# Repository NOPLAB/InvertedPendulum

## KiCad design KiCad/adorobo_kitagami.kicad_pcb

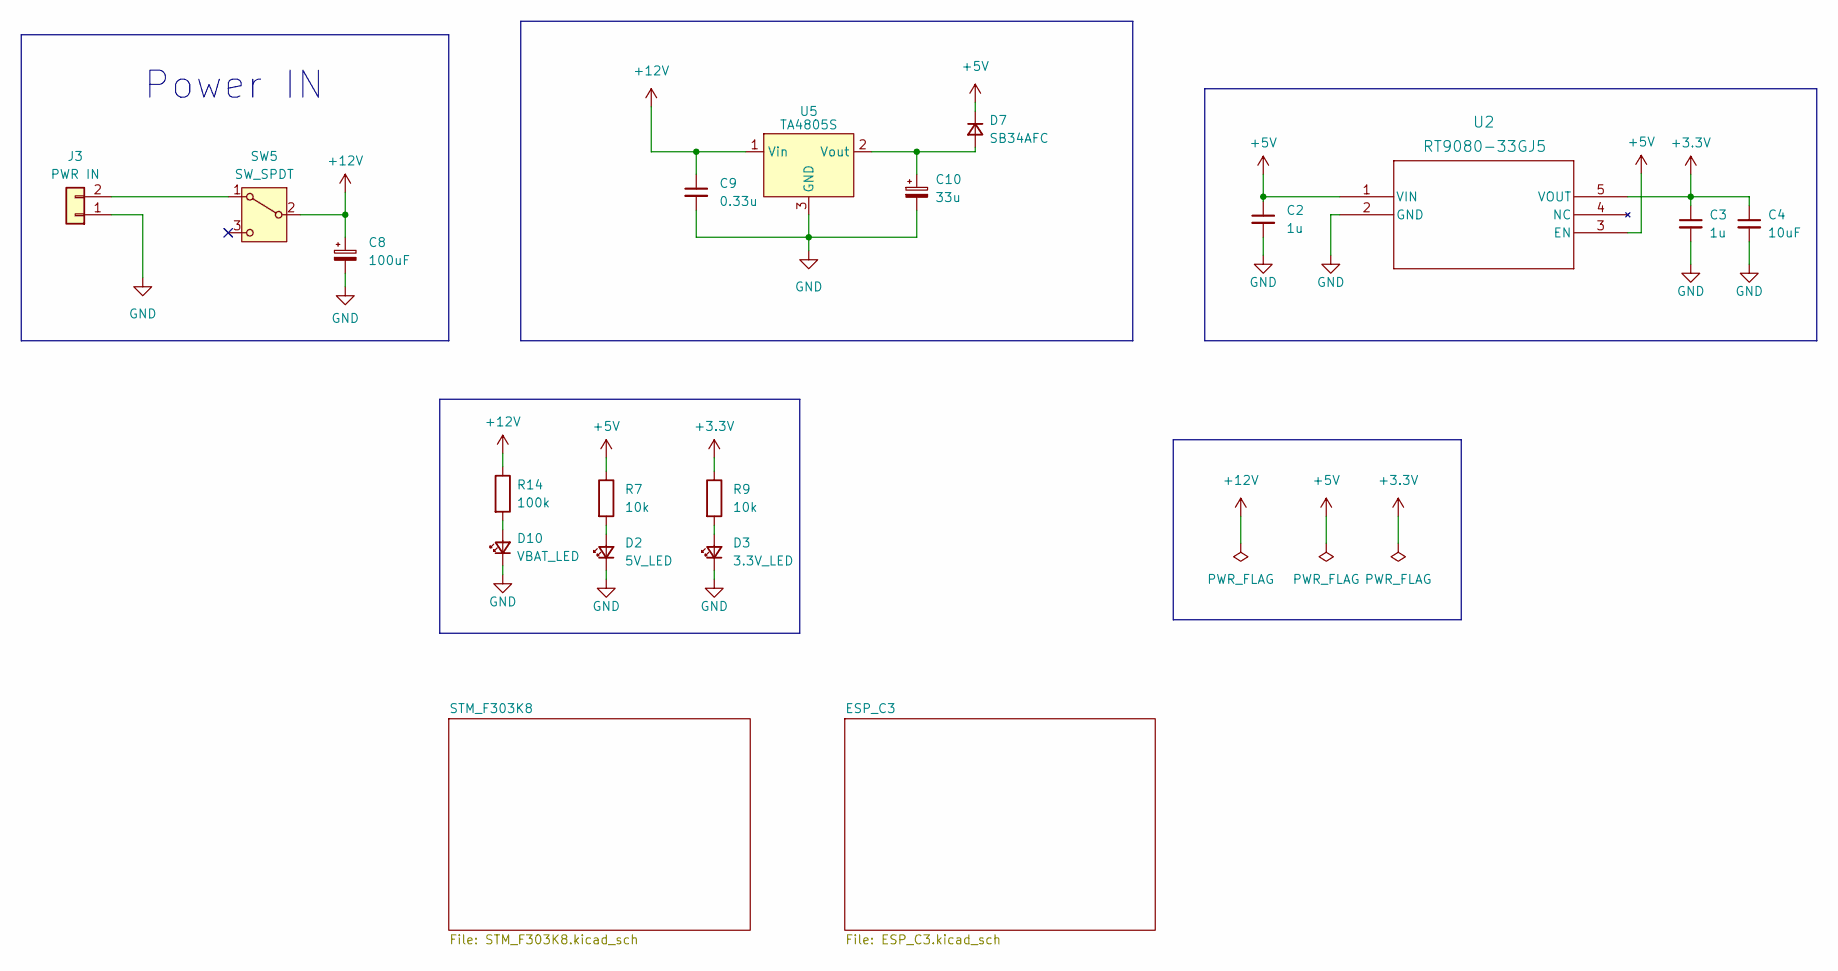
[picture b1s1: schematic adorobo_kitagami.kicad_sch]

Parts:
C2, C3: 1u; C_0603_1608Metric_Pad1.08x0.95mm_HandSolder
C4: 10uF; C_0805_2012Metric_Pad1.18x1.45mm_HandSolder
C8: 100uF; CP_Radial_D5.0mm_P2.00mm
C9: 0.33u; C_Radial_D10.0mm_H12.5mm_P5.00mm
C10: 33u; CP_Radial_D5.0mm_P2.00mm
D2: 5V_LED; LED_0603_1608Metric_Pad1.05x0.95mm_HandSolder
D3: 3.3V_LED; LED_0603_1608Metric_Pad1.05x0.95mm_HandSolder
D7: SB34AFC; SODFL4725X110N
D10: VBAT_LED; LED_0603_1608Metric_Pad1.05x0.95mm_HandSolder
J3: PWR IN; JST_XA_B02B-XASK-1_1x02_P2.50mm_Vertical
R7, R9: 10k; R_0603_1608Metric_Pad0.98x0.95mm_HandSolder
R14: 100k; R_0603_1608Metric_Pad0.98x0.95mm_HandSolder
SW5: SW_SPDT; 2MS1T1B4VS2QES
U2: RT9080-33GJ5
U5: TA4805S

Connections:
+3.3V: C3.1, C4.1, R9.1, U2.5 (VOUT); also elsewhere on the board
+5V: C2.1, D7.1 (K), R7.1, U2.1 (VIN), U2.3 (EN); also elsewhere on the board
+12V: C8.1, C9.1, R14.1, SW5.2 (B), U5.1 (Vin); also elsewhere on the board
GND: C2.2, C3.2, C4.2, C8.2, C9.2, C10.2, D2.1 (K), D3.1 (K), D10.1 (K), J3.1, U2.2 (GND), U5.3 (GND); also elsewhere on the board
unnamed: D2.2 (A), R7.2
unnamed: D3.2 (A), R9.2
unnamed: C10.1, D7.2 (A), U5.2 (Vout)
unnamed: D10.2 (A), R14.2
unnamed: J3.2, SW5.1 (A)

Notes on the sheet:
Power IN

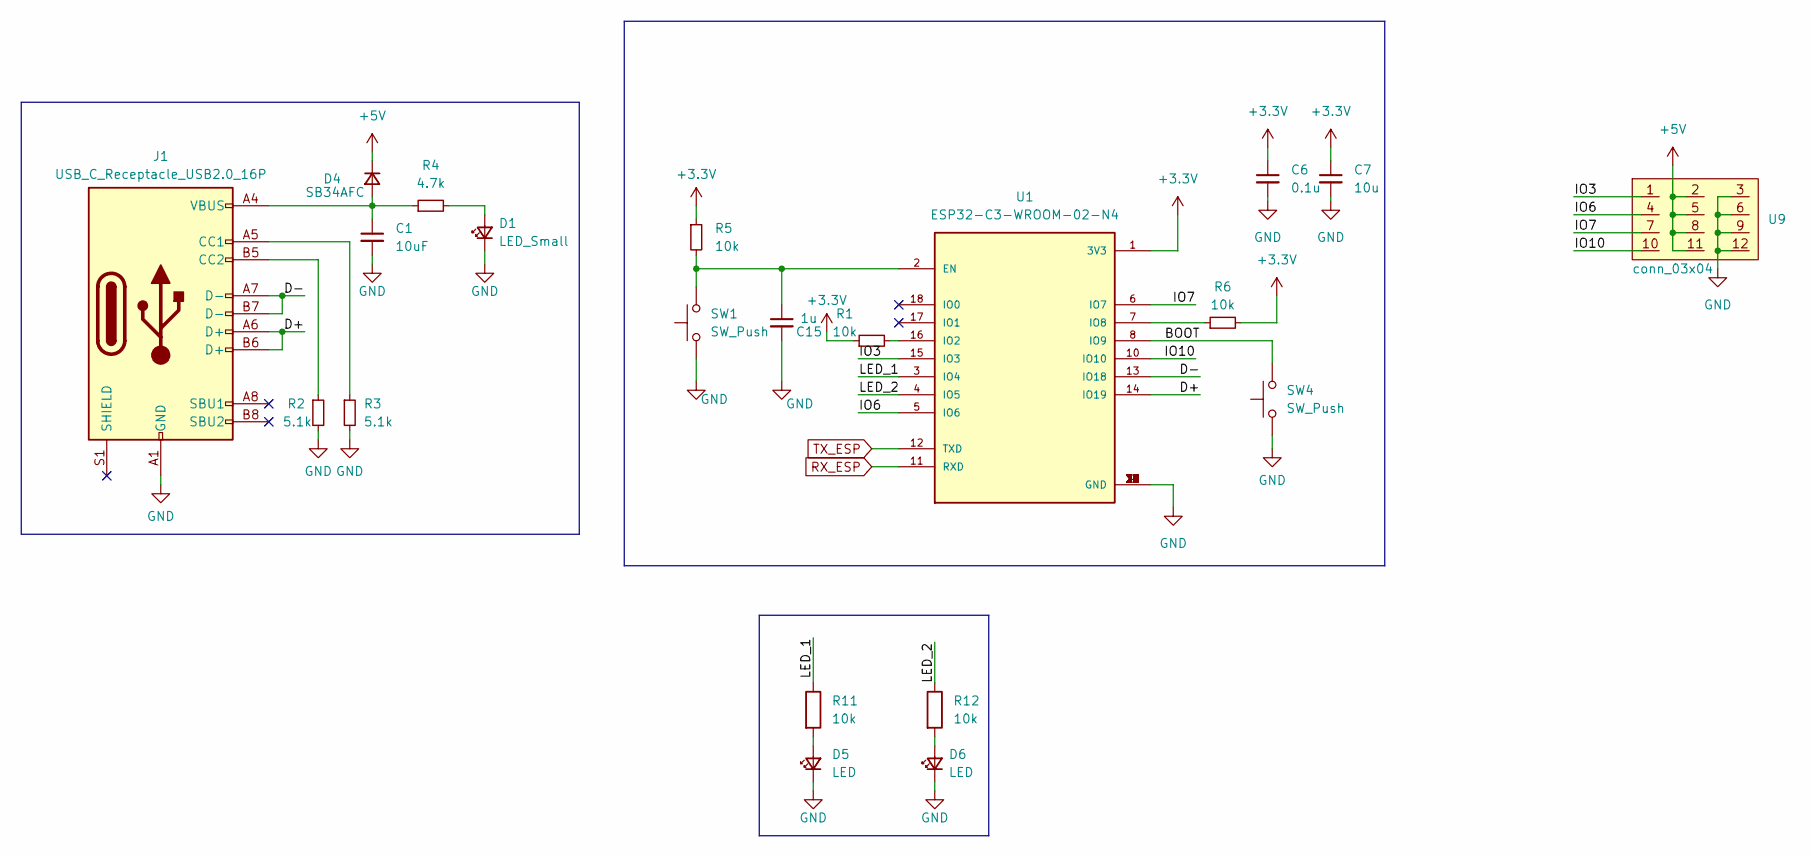
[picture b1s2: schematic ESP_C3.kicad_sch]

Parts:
C1: 10uF; R_0805_2012Metric_Pad1.20x1.40mm_HandSolder
C6: 0.1u; C_0603_1608Metric_Pad1.08x0.95mm_HandSolder
C7: 10u; R_0805_2012Metric_Pad1.20x1.40mm_HandSolder
C15: 1u; C_0603_1608Metric_Pad1.08x0.95mm_HandSolder
D1: LED_Small; LED_0603_1608Metric_Pad1.05x0.95mm_HandSolder
D4: SB34AFC; SODFL4725X110N
D5, D6: LED; LED_0603_1608Metric_Pad1.05x0.95mm_HandSolder
J1: USB_C_Receptacle_USB2.0_16P; HCTYPEC16PCB10
R1, R5, R6, R11, R12: 10k; R_0603_1608Metric_Pad0.98x0.95mm_HandSolder
R2, R3: 5.1k; R_0603_1608Metric_Pad0.98x0.95mm_HandSolder
R4: 4.7k; R_0603_1608Metric_Pad0.98x0.95mm_HandSolder
SW1, SW4: SW_Push; SKRPACE010
U1: ESP32-C3-WROOM-02-N4; MODULE_ESP32-C3-WROOM-02-H4
U9: conn_03x04; conn_03x04_pinn

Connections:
+3.3V: C6.1, C7.1, R1.1, R5.1, R6.2, U1.1 (3V3); also elsewhere on the board
+5V: D4.1 (K), U9.2, U9.5, U9.8, U9.11; also elsewhere on the board
/ESP_C3/BOOT: SW4.2, U1.8 (IO9)
/ESP_C3/D+: J1.A6 (D+), J1.B6 (D+), U1.14 (IO19)
/ESP_C3/D-: J1.A7 (D-), J1.B7 (D-), U1.13 (IO18)
/ESP_C3/IO3: U1.15 (IO3), U9.1
/ESP_C3/IO6: U1.5 (IO6), U9.4
/ESP_C3/IO7: U1.6 (IO7), U9.7
/ESP_C3/IO10: U1.10 (IO10), U9.10
/ESP_C3/LED_1: R11.1, U1.3 (IO4)
/ESP_C3/LED_2: R12.1, U1.4 (IO5)
GND: C1.2, C6.2, C7.2, C15.2, D1.1 (K), D5.1 (K), D6.1 (K), J1.A1 (GND), J1.A12 (GND), J1.B1 (GND), J1.B12 (GND), R2.2, R3.2, SW1.1, SW4.1, U1.9 (GND), U1.19 (GND), U1.20 (GND), U1.21 (GND), U1.22 (GND), U1.23 (GND), U1.24 (GND), U1.25 (GND), U1.26 (GND), U1.27 (GND), U1.28 (GND), U1.29 (GND), U1.30 (GND), U1.31 (GND), U1.32 (GND), U1.33 (GND), U1.34 (GND), U1.35 (GND), U1.36 (GND), U1.37 (GND), U1.38 (GND), U1.39 (GND), U9.3, U9.6, U9.9, U9.12; also elsewhere on the board
unnamed: D1.2 (A), R4.2
unnamed: C1.1, D4.2 (A), J1.A4 (VBUS), J1.A9 (VBUS), J1.B4 (VBUS), J1.B9 (VBUS), R4.1
unnamed: D5.2 (A), R11.2
unnamed 45: D6.2 (A), R12.2; also elsewhere on the board
unnamed: J1.A5 (CC1), R3.1
unnamed: J1.B5 (CC2), R2.1
unnamed: C15.1, R5.2, SW1.2, U1.2 (EN)
unnamed: R1.2, U1.16 (IO2)
unnamed: R6.1, U1.7 (IO8)
RX_ESP: U1.11 (RXD); also elsewhere on the board
TX_ESP: U1.12 (TXD); also elsewhere on the board

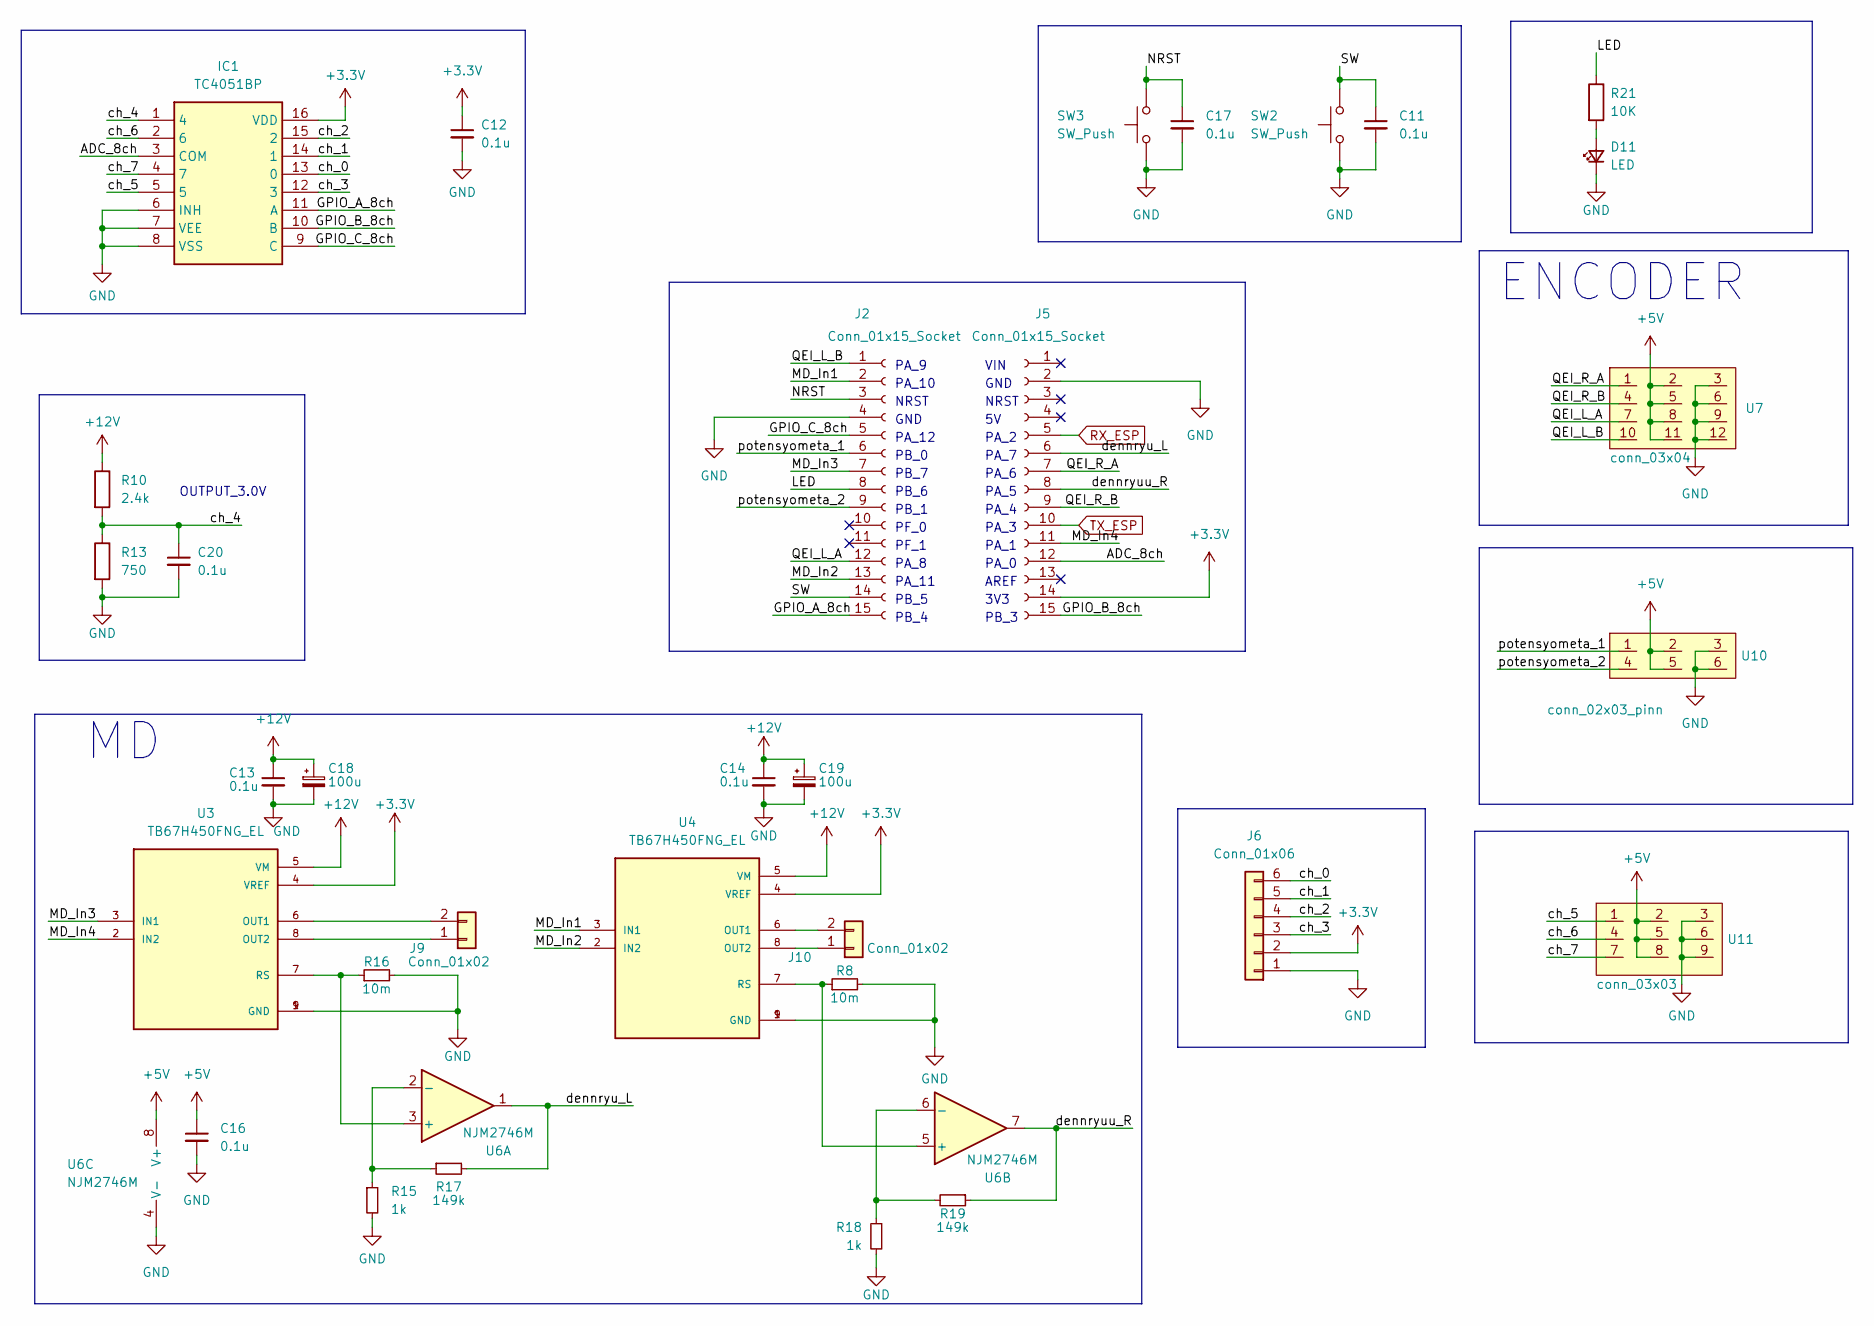
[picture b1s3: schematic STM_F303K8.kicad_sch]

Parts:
C11, C12, C13, C14, C16, C17, C20: 0.1u; C_0603_1608Metric_Pad1.08x0.95mm_HandSolder
C18, C19: 100u; CP_Radial_D5.0mm_P2.00mm
D11: LED; LED_0603_1608Metric_Pad1.05x0.95mm_HandSolder
IC1: TC4051BP; DIP762W60P254L1925H445Q16N; Manufacturer_Part_Number TC4051BP; Mouser Part Number N/A
J2, J5: Conn_01x15_Socket; PinSocket_1x15_P2.54mm_Vertical
J6: Conn_01x06; JST_PH_B6B-PH-K_1x06_P2.00mm_Vertical
J9, J10: Conn_01x02; JST_XA_B02B-XASK-1_1x02_P2.50mm_Vertical
R8, R16: 10m; SL1TER010F
R10: 2.4k; R_0603_1608Metric_Pad0.98x0.95mm_HandSolder
R13: 750; R_0603_1608Metric_Pad0.98x0.95mm_HandSolder
R15, R18: 1k; R_0603_1608Metric_Pad0.98x0.95mm_HandSolder
R17, R19: 149k; R_0603_1608Metric_Pad0.98x0.95mm_HandSolder
R21: 10K; R_0603_1608Metric_Pad0.98x0.95mm_HandSolder
SW2, SW3: SW_Push; DTS63NV
U3, U4: TB67H450FNG_EL; SOIC127P599X175-9N
U6: NJM2746M
U7: conn_03x04; conn_03x04_pinn
U10: conn_02x03_pinn; PinHeader_2x03_P2.54mm_Vertical
U11: conn_03x03

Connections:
+3.3V: C12.1, IC1.16 (VDD), J5.1, J5.14, J6.2, U3.4 (VREF), U4.4 (VREF); also elsewhere on the board
+5V: C16.1, U6.8 (V+), U7.2, U7.5, U7.8, U7.11, U10.2, U10.5, U11.2, U11.5, U11.8; also elsewhere on the board
+12V: C13.1, C14.1, C18.1, C19.1, R10.1, U3.5 (VM), U4.5 (VM); also elsewhere on the board
/STM_F303K8/ADC_8ch: IC1.3 (COM), J5.12
/STM_F303K8/GPIO_A_8ch: IC1.11 (A), J2.15
/STM_F303K8/GPIO_B_8ch: IC1.10 (B), J5.15
/STM_F303K8/GPIO_C_8ch: IC1.9 (C), J2.5
/STM_F303K8/LED: J2.8, R21.1
/STM_F303K8/MD_In1: J2.2, U4.3 (IN1)
/STM_F303K8/MD_In2: J2.13, U4.2 (IN2)
/STM_F303K8/MD_In3: J2.7, U3.3 (IN1)
/STM_F303K8/MD_In4: J5.11, U3.2 (IN2)
/STM_F303K8/NRST: C17.1, J2.3, SW3.2
/STM_F303K8/QEI_L_A: J2.12, U7.7
/STM_F303K8/QEI_L_B: J2.1, U7.10
/STM_F303K8/QEI_R_A: J5.7, U7.1
/STM_F303K8/QEI_R_B: J5.9, U7.4
/STM_F303K8/SW: C11.1, J2.14, SW2.2
/STM_F303K8/ch_0: IC1.13 (0), J6.6
/STM_F303K8/ch_1: IC1.14 (1), J6.5
/STM_F303K8/ch_2: IC1.15 (2), J6.4
/STM_F303K8/ch_3: IC1.12 (3), J6.3
/STM_F303K8/ch_4: C20.1, IC1.1 (4), R10.2, R13.1
/STM_F303K8/ch_5: IC1.5, U11.1
/STM_F303K8/ch_6: IC1.2 (6), U11.4
/STM_F303K8/ch_7: IC1.4 (7), U11.7
/STM_F303K8/dennryu_L: J5.6, R17.2, U6.1
/STM_F303K8/dennryuu_R: J5.8, R19.1, U6.7
/STM_F303K8/potensyometa_1: J2.6, U10.1
/STM_F303K8/potensyometa_2: J2.9, U10.4
GND: C11.2, C12.2, C13.2, C14.2, C16.2, C17.2, C18.2, C19.2, C20.2, D11.1 (K), IC1.6 (INH), IC1.7 (VEE), IC1.8 (VSS), J2.4, J5.2, J6.1, R8.2, R13.2, R15.2, R16.2, R18.2, SW2.1, SW3.1, U3.1 (GND), U3.9 (GND), U4.1 (GND), U4.9 (GND), U6.4 (V-), U7.3, U7.6, U7.9, U7.12, U10.3, U10.6, U11.3, U11.6, U11.9; also elsewhere on the board
unnamed: D11.2 (A), R21.2
unnamed: J9.1, U3.8 (OUT2)
unnamed: J9.2, U3.6 (OUT1)
unnamed: J10.1, U4.8 (OUT2)
unnamed: J10.2, U4.6 (OUT1)
unnamed: R16.1, U3.7 (RS), U6.3 (+)
unnamed: R8.1, U4.7 (RS), U6.5 (+)
unnamed: R15.1, R17.1, U6.2 (-)
unnamed: R18.1, R19.2, U6.6 (-)
RX_ESP: J5.5; also elsewhere on the board
TX_ESP: J5.10; also elsewhere on the board

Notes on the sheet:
GND
PB_0
PF_0
PA_7
PA_9
PA_0
PB_6
AREF
VIN
PA_2
PA_1
PA_4
PA_10
PA_8
OUTPUT_3.0V
PB_3
PA_12
PB_7
PB_4
PF_1
NRST
PA_11
PB_5
PA_5
3V3
PA_3
ENCODER
PB_1
PA_6

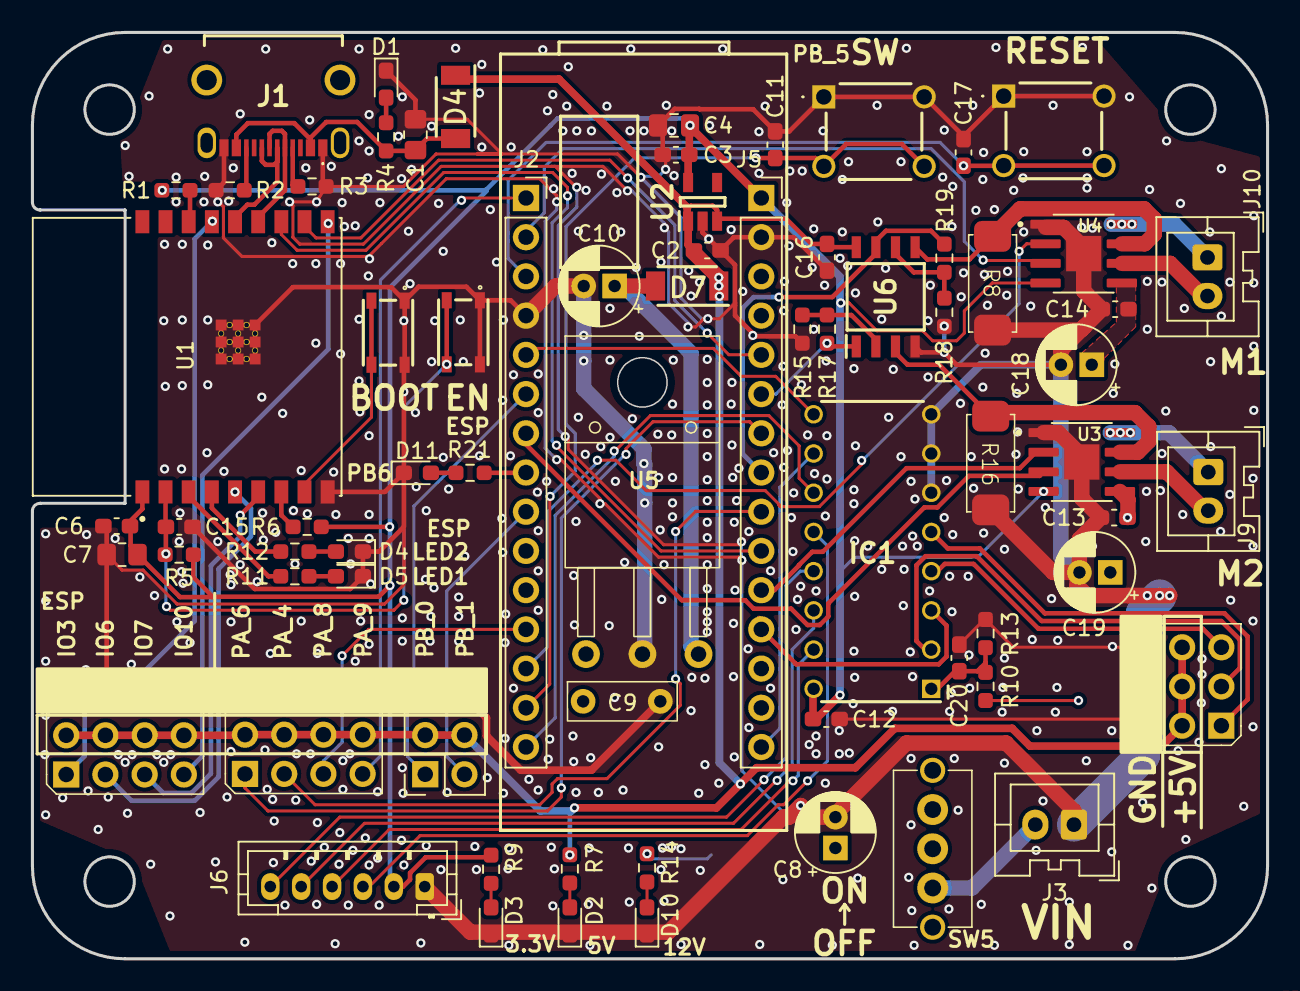
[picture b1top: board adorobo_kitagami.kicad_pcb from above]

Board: 2 copper layers, 80.0 x 60.0 mm, 71 parts (0 on the bottom side), 65 nets.

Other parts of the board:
D4#2: LED; LED_0603_1608Metric_Pad1.05x0.95mm_HandSolder

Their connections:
GND: D4#2.1 (K); also elsewhere on the board
unnamed 45: D4#2.2 (A); also elsewhere on the board

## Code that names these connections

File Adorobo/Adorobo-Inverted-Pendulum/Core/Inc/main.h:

/* USER CODE BEGIN Header */
/**
  ******************************************************************************
  * @file           : main.h
  * @brief          : Header for main.c file.
  *                   This file contains the common defines of the application.
  ******************************************************************************
  * @attention
  *
  * Copyright (c) 2025 STMicroelectronics.
  * All rights reserved.
  *
  * This software is licensed under terms that can be found in the LICENSE file
  * in the root directory of this software component.
  * If no LICENSE file comes with this software, it is provided AS-IS.
  *
  ******************************************************************************
  */
/* USER CODE END Header */

/* Define to prevent recursive inclusion -------------------------------------*/
#ifndef __MAIN_H
#define __MAIN_H

#ifdef __cplusplus
extern "C" {
#endif

/* Includes ------------------------------------------------------------------*/
#include "stm32f3xx_hal.h"

/* Private includes ----------------------------------------------------------*/
/* USER CODE BEGIN Includes */

/* USER CODE END Includes */

/* Exported types ------------------------------------------------------------*/
/* USER CODE BEGIN ET */

/* USER CODE END ET */

/* Exported constants --------------------------------------------------------*/
/* USER CODE BEGIN EC */

/* USER CODE END EC */

/* Exported macro ------------------------------------------------------------*/
/* USER CODE BEGIN EM */

/* USER CODE END EM */

void HAL_TIM_MspPostInit(TIM_HandleTypeDef *htim);

/* Exported functions prototypes ---------------------------------------------*/
void Error_Handler(void);

/* USER CODE BEGIN EFP */

/* USER CODE END EFP */

/* Private defines -----------------------------------------------------------*/
#define QEI_R_B_Pin GPIO_PIN_0
#define QEI_R_B_GPIO_Port GPIOF
#define QEI_R_B_EXTI_IRQn EXTI0_IRQn
#define ADC1_Pin GPIO_PIN_0
#define ADC1_GPIO_Port GPIOA
#define MD_In3_Pin GPIO_PIN_1
#define MD_In3_GPIO_Port GPIOA
#define VCP_TX_Pin GPIO_PIN_2
#define VCP_TX_GPIO_Port GPIOA
#define MD_In4_Pin GPIO_PIN_3
#define MD_In4_GPIO_Port GPIOA
#define Button_R_Pin GPIO_PIN_0
#define Button_R_GPIO_Port GPIOB
#define QEI_L_A_Pin GPIO_PIN_12
#define QEI_L_A_GPIO_Port GPIOA
#define QEI_L_A_EXTI_IRQn EXTI15_10_IRQn
#define SWDIO_Pin GPIO_PIN_13
#define SWDIO_GPIO_Port GPIOA
#define SWCLK_Pin GPIO_PIN_14
#define SWCLK_GPIO_Port GPIOA
#define VCP_RX_Pin GPIO_PIN_15
#define VCP_RX_GPIO_Port GPIOA
#define LED_Pin GPIO_PIN_3
#define LED_GPIO_Port GPIOB
#define MD_In1_Pin GPIO_PIN_4
#define MD_In1_GPIO_Port GPIOB
#define MD_In2_Pin GPIO_PIN_5
#define MD_In2_GPIO_Port GPIOB
#define QEI_R_A_Pin GPIO_PIN_6
#define QEI_R_A_GPIO_Port GPIOB
#define QEI_R_A_EXTI_IRQn EXTI9_5_IRQn
#define QEI_L_B_Pin GPIO_PIN_7
#define QEI_L_B_GPIO_Port GPIOB
#define QEI_L_B_EXTI_IRQn EXTI9_5_IRQn

/* USER CODE BEGIN Private defines */

/* USER CODE END Private defines */

#ifdef __cplusplus
}
#endif

#endif /* __MAIN_H */

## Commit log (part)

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2025-06-09 ignore cache
2025-06-09 add README.md
2025-06-09 setup MATLAB project
2025-06-09 add explanation about clc
2025-06-10 Add Inverted Pendulum Model
2025-06-12 Update Models
2025-06-12 add lqr_sample
2025-06-17 add system identification about robot program
2025-06-21 WIP MATLAB
2025-06-26 MATLAB Update
2025-06-30 Update Scripts
2025-07-01 Update MATLAB
2025-07-01 STM32 first commit
2025-07-01 fix bux
2025-07-01 mv interrupt handler
2025-07-01 timer interrupt
2025-07-01 fix author
2025-07-01 include guard
2025-07-01 STM32 timer6 1000Hz interrupt
2025-07-01 interval timer
2025-07-01 fix able to compile
2025-07-01 fix able to run
2025-07-01 first adc convert
2025-07-01 motor
2025-07-04 MATLAB State Feedback
2025-07-04 add Claude
2025-07-06 current feedback
2025-07-06 speed feedback
2025-07-07 Add renovate.json
2025-07-07 動いた記念
2025-07-10 MIT Adaptive Controller
2025-07-10 Update Template
2025-07-10 Update PR Checks
2025-07-10 Append auto format script
2025-07-10 Add .gitignore. Fix GitHub Actions
2025-07-10 add KiCad
2025-07-10 new rust project
2025-07-10 Clock configuration
2025-07-11 I have documented the changes made.
2025-07-12 電流制御
2025-07-12 リファクタリング
2025-07-12 Adaptive
2025-07-12 Change params
2025-07-12 Update documentation
2025-07-13 init inference-onnx
2025-07-13 ort init
2025-07-13 first inference
2025-07-13 Refactoring
2025-07-13 Fix bug
2025-07-13 UART Mode
2025-07-13 ライントレースプログラム
2025-07-14 Run ONNX model
2025-07-14 Update controller
2025-07-14 Git hook
2025-08-06 Update actions/download-artifact action to v5
2025-08-16 Update actions/checkout action to v5
2026-03-01 Update GitHub Artifact Actions
